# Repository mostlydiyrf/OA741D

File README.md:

# OA741D
Reference documents and Kicad (ver.6) design files.

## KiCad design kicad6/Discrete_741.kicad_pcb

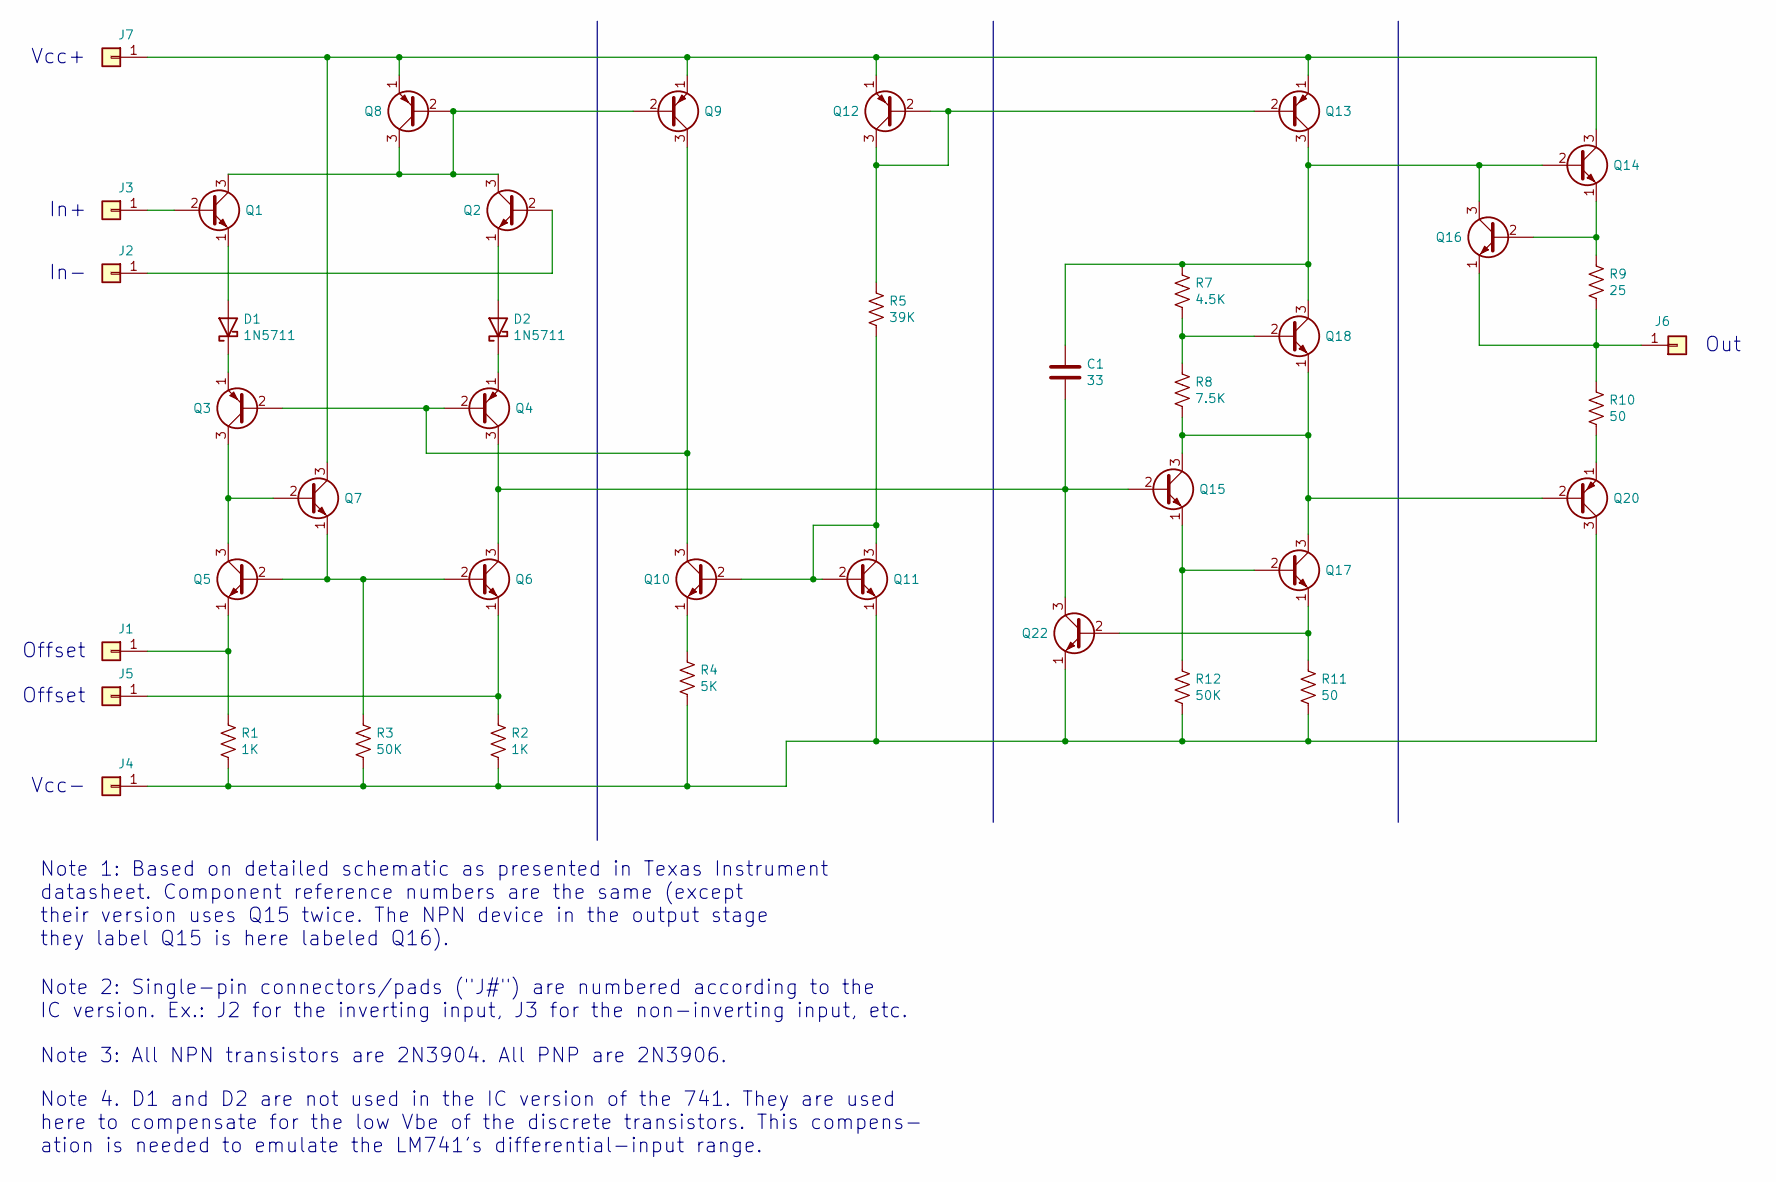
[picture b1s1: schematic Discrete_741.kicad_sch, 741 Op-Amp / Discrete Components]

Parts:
C1: 33; Ceramic_Disk_Capacitor_P5.00mm
D1, D2: 1N5711; D_DO-15_P5.08mm_Vertical_KathodeUp
J1, J2, J3, J4, J5, J6, J7: Conn_01x01; PinHeader_1x01_P2.54mm_Vertical
Q1, Q2, Q5, Q6, Q7, Q10, Q11, Q14, Q15, Q16, Q17, Q18, Q22: 2N3904; TO-92_Inline
Q3, Q4, Q8, Q9, Q12, Q13, Q20: 2N3906; TO-92_Inline
R1, R2: 1K; R_Axial_DIN0207_L6.3mm_D2.5mm_P5.08mm_Vertical
R3, R12: 50K; R_Axial_DIN0207_L6.3mm_D2.5mm_P5.08mm_Vertical
R4: 5K; R_Axial_DIN0207_L6.3mm_D2.5mm_P5.08mm_Vertical
R5: 39K; R_Axial_DIN0207_L6.3mm_D2.5mm_P5.08mm_Vertical
R7: 4.5K; R_Axial_DIN0207_L6.3mm_D2.5mm_P5.08mm_Vertical
R8: 7.5K; R_Axial_DIN0207_L6.3mm_D2.5mm_P5.08mm_Vertical
R9: 25; R_Axial_DIN0207_L6.3mm_D2.5mm_P5.08mm_Vertical
R10, R11: 50; R_Axial_DIN0207_L6.3mm_D2.5mm_P5.08mm_Vertical

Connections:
unnamed: C1.1, Q13.3 (C), Q14.2 (B), Q16.3 (C), Q18.3 (C), R7.1
unnamed: C1.2, Q4.3 (C), Q6.3 (C), Q15.2 (B), Q22.3 (C)
unnamed: D1.1 (K), Q3.1 (E)
unnamed: D1.2 (A), Q1.1 (E)
unnamed: D2.1 (K), Q4.1 (E)
unnamed: D2.2 (A), Q2.1 (E)
unnamed: J1.1, Q5.1 (E), R1.1
unnamed: J2.1, Q2.2 (B)
unnamed: J3.1, Q1.2 (B)
unnamed: J4.1, Q11.1 (E), Q20.3 (C), Q22.1 (E), R1.2, R2.2, R3.2, R4.2, R11.2, R12.2
unnamed: J5.1, Q6.1 (E), R2.1
unnamed: J6.1, Q16.1 (E), R9.2, R10.1
unnamed: J7.1, Q7.3 (C), Q8.1 (E), Q9.1 (E), Q12.1 (E), Q13.1 (E), Q14.3 (C)
unnamed: Q1.3 (C), Q2.3 (C), Q8.2 (B), Q8.3 (C), Q9.2 (B)
unnamed: Q3.3 (C), Q5.3 (C), Q7.2 (B)
unnamed: Q5.2 (B), Q6.2 (B), Q7.1 (E), R3.1
unnamed: Q10.1 (E), R4.1
unnamed: Q10.2 (B), Q11.2 (B), Q11.3 (C), R5.2
unnamed: Q3.2 (B), Q4.2 (B), Q9.3 (C), Q10.3 (C)
unnamed: Q12.2 (B), Q12.3 (C), Q13.2 (B), R5.1
unnamed: Q14.1 (E), Q16.2 (B), R9.1
unnamed: Q15.1 (E), Q17.2 (B), R12.1
unnamed: Q15.3 (C), Q17.3 (C), Q18.1 (E), Q20.2 (B), R8.2
unnamed: Q17.1 (E), Q22.2 (B), R11.1
unnamed: Q18.2 (B), R7.2, R8.1
unnamed: Q20.1 (E), R10.2

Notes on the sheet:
Vcc-
Out
Note 1: Based on detailed schematic as presented in Texas Instrument datasheet. Component reference numbers are the same (except their version uses Q15 twice. The NPN device in the output stage they label Q15 is here labeled Q16).
Note 3: All NPN transistors are 2N3904. All PNP are 2N3906.
Offset
Note 4. D1 and D2 are not used in the IC version of the 741. They are used here to compensate for the low Vbe of the discrete transistors. This compens- ation is needed to emulate the LM741's differential-input range.
Vcc+
In+
Note 2: Single-pin connectors/pads ("J#") are numbered according to the IC version. Ex.: J2 for the inverting input, J3 for the non-inverting input, etc.
In-

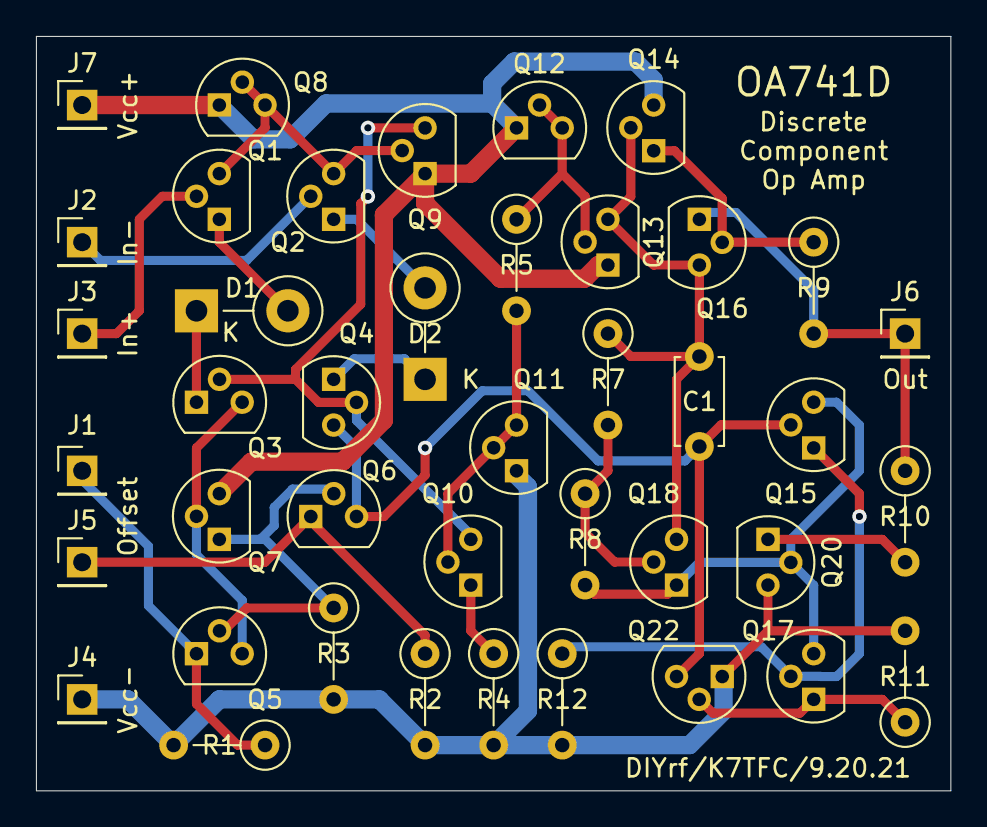
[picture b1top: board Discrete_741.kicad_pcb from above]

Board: 2 copper layers, 50.8 x 41.9 mm, 41 parts (0 on the bottom side), 26 nets.
